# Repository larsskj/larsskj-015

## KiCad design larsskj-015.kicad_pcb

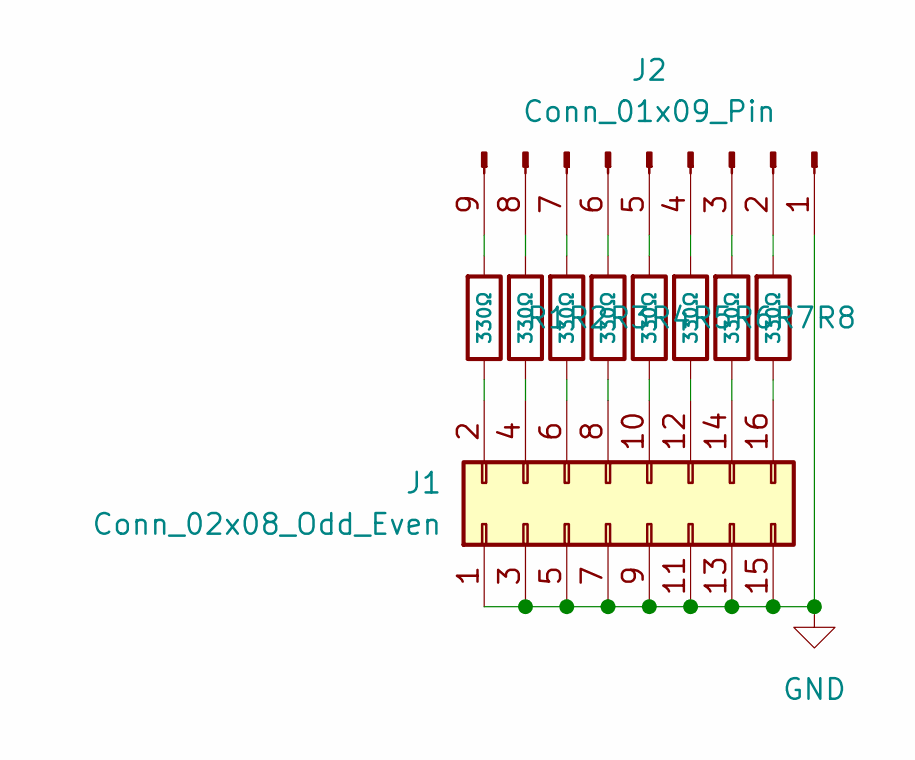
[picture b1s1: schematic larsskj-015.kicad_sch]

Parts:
J1: Conn_02x08_Odd_Even; PinHeader_2x08_P1.27mm_Vertical
J2: Conn_01x09_Pin; PinHeader_1x09_P1.27mm_Vertical
R1, R2, R3, R4, R5, R6, R7, R8: 330Ω; R_0402; Overload Voltage (Max) 50V; Tolerance ±1%; Part 0402WGF3300TCE; LCSC C25104

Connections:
GND: J1.1, J1.3, J1.5, J1.7, J1.9, J1.11, J1.13, J1.15, J2.1
unnamed: J1.2, R1.2
unnamed: J1.4, R2.2
unnamed: J1.6, R3.2
unnamed: J1.8, R4.2
unnamed: J1.10, R5.2
unnamed: J1.12, R6.2
unnamed: J1.14, R7.2
unnamed: J1.16, R8.2
unnamed: J2.2, R8.1
unnamed: J2.3, R7.1
unnamed: J2.4, R6.1
unnamed: J2.5, R5.1
unnamed: J2.6, R4.1
unnamed: J2.7, R3.1
unnamed: J2.8, R2.1
unnamed: J2.9, R1.1

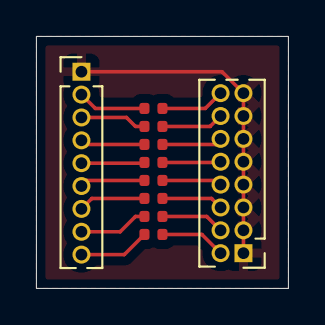
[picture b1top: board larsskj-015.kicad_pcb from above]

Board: 2 copper layers, 14.0 x 14.0 mm, 10 parts (0 on the bottom side), 17 nets.

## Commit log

2025-10-26 Ready for release
